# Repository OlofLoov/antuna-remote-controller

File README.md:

# Renders

One folder per commit, made by `scripts/render.sh` in CI.
Main first, then each pull request; newest commit first.

# main

## 2026-11-28-1006-49a1b0d

## 2026-11-28-1005-fa91d10

## 2026-11-27-1953-4381ade

## 2026-11-27-1953-3425ad4

## 2026-11-27-1953-1f563c3

## 2026-11-26-1312-f647dff

# pr-9

## 2026-11-28-0048-dfe2b04

# pr-8

## 2026-11-27-2004-0030056

# pr-7

## 2026-11-27-1953-70339c3

## 2026-11-27-1838-97ce40e

# pr-6

## 2026-11-27-1420-0593183

# pr-5

## 2026-11-27-1420-341aa33

## 2026-11-27-0927-84beafe

## 2026-11-26-1752-6897d9c

## 2026-11-26-1507-de8bec9

## 2026-11-26-1450-7849190

## 2026-11-26-1448-b4e9cd6

## 2026-11-26-1445-7078558

## 2026-11-26-1322-503d36b

# pr-4

## ba047ec

## 66d7c0c

# pr-3

## b4d252e

## 2026-11-26-1310-69a1c93

## 2026-11-26-1310-65226cf

## 2026-11-26-1308-f975772

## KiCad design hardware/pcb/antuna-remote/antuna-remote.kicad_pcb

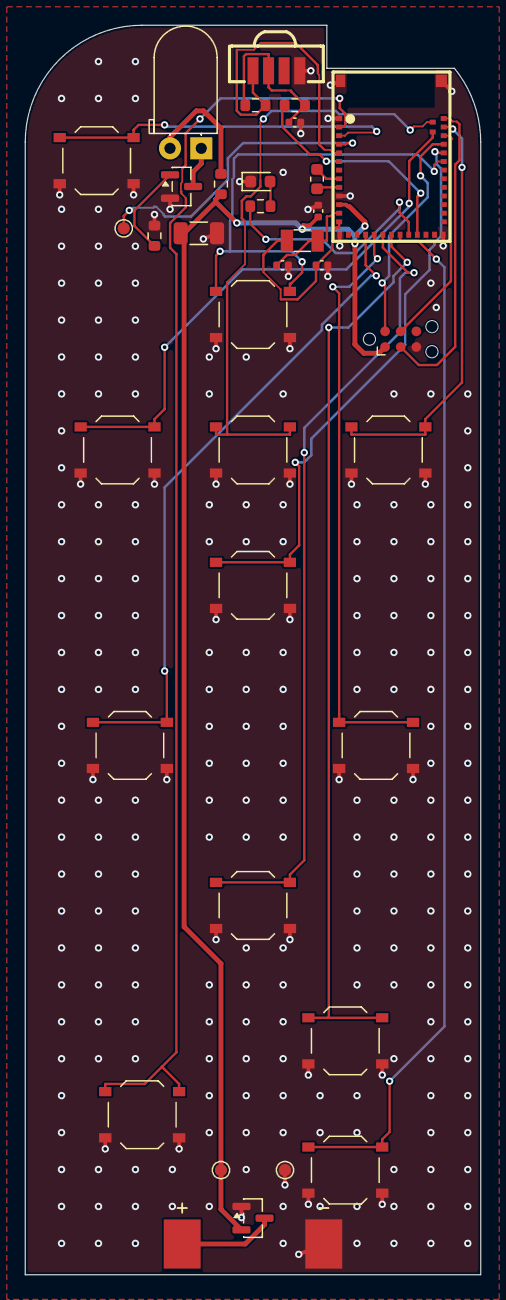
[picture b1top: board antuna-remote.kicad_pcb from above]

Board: 2 copper layers, 37.0 x 101.5 mm, 35 parts (0 on the bottom side), 30 nets.

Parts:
BT1: 2 x AAA; Keystone_AAAx2_EdgeTabs
C1: 100uF; C_1206_3216Metric
C2, C5: 4.7uF; C_0402_1005Metric
C3, C4: DNP; C_0402_1005Metric
D1: TSAL6200; LED_D5.0mm_Horizontal_O1.27mm_Z3.0mm_IRBlack
D2: Orange; LED_0603_1608Metric
J1: TC2030-NL; Tag-Connect_TC2030-IDC-NL_2x03_P1.27mm_Vertical
L1: 4.7uH; L_0603_1608Metric
Q1: AO3416; SOT-23
Q2: DMP2035U-7; SOT-23
R1: 10; R_0603_1608Metric
R2: 100k; R_0603_1608Metric
R3: 330; R_0603_1608Metric
R4: 100; R_0603_1608Metric
R5: 4.7k; R_0603_1608Metric
SW1: Up; SW_Push_1P1T_XKB_TS-1187A
SW2: Down; SW_Push_1P1T_XKB_TS-1187A
SW3: Left; SW_Push_1P1T_XKB_TS-1187A
SW4: Right; SW_Push_1P1T_XKB_TS-1187A
SW5: Select; SW_Push_1P1T_XKB_TS-1187A
SW6: Back; SW_Push_1P1T_XKB_TS-1187A
SW7: Home; SW_Push_1P1T_XKB_TS-1187A
SW8: Play; SW_Push_1P1T_XKB_TS-1187A
SW9: Volup; SW_Push_1P1T_XKB_TS-1187A
SW10: Voldn; SW_Push_1P1T_XKB_TS-1187A
SW11: Mute; SW_Push_1P1T_XKB_TS-1187A
SW12: Power; SW_Push_1P1T_XKB_TS-1187A
TP1: VBAT; TestPoint_Pad_D1.0mm
TP2: GND; TestPoint_Pad_D1.0mm
TP3: IR gate; TestPoint_Pad_D1.0mm
U1: AN54LQ-15; Raytac_AN54LQ-15
U2: TSMP96000; Vishay_TSMP96000TR
Y1: 32.768kHz; Crystal_SMD_3215-2Pin_3.2x1.5mm

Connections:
/BAT+: BT1.1, Q2.3
/DCC: L1.1, U1.9
/DECD: L1.2, U1.8
/GND: BT1.2, C1.2, C2.2, C3.2, C4.2, C5.2, D2.1, J1.5, Q1.2, Q2.1, R2.2, SW1.2, SW2.2, SW3.2, SW4.2, SW5.2, SW6.2, SW7.2, SW8.2, SW9.2, SW10.2, SW11.2, SW12.2, TP2.1, U1.1, U1.10, U1.14, U1.26, U1.42, U1.43, U2.1
/IR_A: D1.2, R1.2
/IR_K: D1.1, Q1.3
/IR_LED: Q1.1, R2.1, TP3.1, U1.4
/IR_RX: R5.2, U1.5, U2.4
/IR_RX_PWR: R4.1, U1.23
/IR_VS: C5.1, R4.2, R5.1, U2.3
/KEY_BACK: SW6.1, U1.17
/KEY_DOWN: SW2.1, U1.35
/KEY_HOME: SW7.1, U1.18
/KEY_LEFT: SW3.1, U1.41
/KEY_MUTE: SW11.1, U1.2
/KEY_PLAY: SW8.1, U1.19
/KEY_POWER: SW12.1, U1.3
/KEY_RIGHT: SW4.1, U1.38
/KEY_SELECT: SW5.1, U1.40
/KEY_UP: SW1.1, U1.34
/KEY_VOLDN: SW10.1, U1.21
/KEY_VOLUP: SW9.1, U1.20
/LED_A: D2.2, R3.2
/RESET: J1.3, U1.39
/STATUS_LED: R3.1, U1.22
/SWDCLK: J1.4, U1.37
/SWDIO: J1.2, U1.36
/VBAT: C1.1, C2.1, J1.1, Q2.2, R1.1, TP1.1, U1.11
/XL1: C3.1, U1.12, Y1.1
/XL2: C4.1, U1.13, Y1.2
